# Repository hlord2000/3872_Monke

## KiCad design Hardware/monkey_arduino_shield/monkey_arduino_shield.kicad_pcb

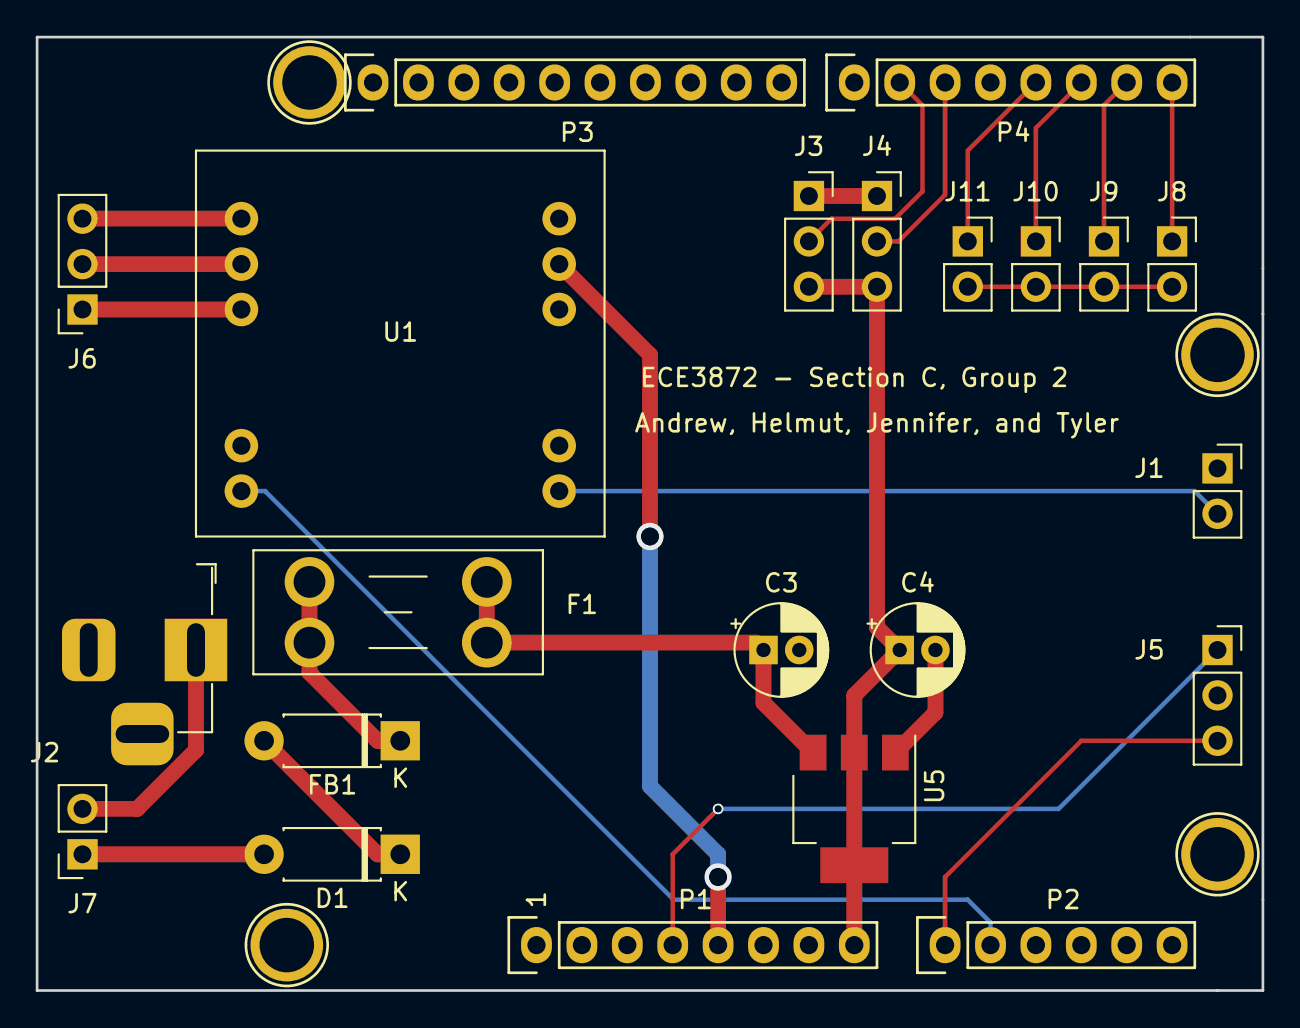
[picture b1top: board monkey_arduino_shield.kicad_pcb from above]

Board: 2 copper layers, 68.6 x 53.3 mm, 26 parts (0 on the bottom side), 21 nets.

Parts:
C3, C4: 10u; CP_Radial_D5.0mm_P2.00mm
D1: B5819W; D_DO-41_SOD81_P7.62mm_Horizontal
F1: 1A; Fuseholder_Blade_Mini_Keystone_3568
FB1: 100 Ohm @ 100 MHz; D_DO-41_SOD81_P7.62mm_Horizontal
J1: Speaker_OUT; PinSocket_1x02_P2.54mm_Vertical
J2: Barrel_Jack; BarrelJack_Horizontal_Helmer_Version
J3: MOTOR_1; PinSocket_1x03_P2.54mm_Vertical
J4: MOTOR_2; PinSocket_1x03_P2.54mm_Vertical
J5: MIC_IN; PinSocket_1x03_P2.54mm_Vertical
J6: POT_IN; PinSocket_1x03_P2.54mm_Vertical
J7: Power_Switch; PinSocket_1x02_P2.54mm_Vertical
J8: IO_Switch_1; PinSocket_1x02_P2.54mm_Vertical
J9: IO_Switch_2; PinSocket_1x02_P2.54mm_Vertical
J10: IO_Switch_3; PinSocket_1x02_P2.54mm_Vertical
J11: IO_Switch_4; PinSocket_1x02_P2.54mm_Vertical
P1: Power; Socket_Strip_Arduino_1x08
P2: Analog; Socket_Strip_Arduino_1x06
P3: Digital; Socket_Strip_Arduino_1x10
P4: Digital; Socket_Strip_Arduino_1x08
P5, P6, P7, P8: CONN_01X01; Arduino_1pin
U1: TPA2005D1-Breakout; TDA_Breakout_Board
U5: AMS1117-5.0; SOT-223-3_TabPin2

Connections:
+3V3: J5.1, P1.4
+5V: P1.5, U1.4
/0(Rx): J8.1, P4.8
/1(Tx): J9.1, P4.7
/2: J10.1, P4.6
/3(**): J11.1, P4.5
/5(**): J4.2, P4.3
/6(**): J3.2, P4.2
/A0: J5.3, P2.1
/A1: P2.2, U1.6
/Vin: C4.1, J3.3, J4.3, P1.8, U5.2
GND: C3.2, C4.2, J1.1, J2.2, J3.1, J4.1, J5.2, J8.2, J9.2, J10.2, J11.2, P1.6, P1.7, P3.4, U1.2, U1.3, U1.7, U5.1
unnamed: C3.1, F1.2, U5.3
unnamed: D1.1, FB1.2
unnamed: D1.2, J7.1
unnamed: F1.1, FB1.1
unnamed: J1.2, U1.1
unnamed: J2.1, J7.2
unnamed: J6.1, U1.8
unnamed: J6.2, U1.9
unnamed: J6.3, U1.10

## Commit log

2021-09-21 dded BOM
2021-09-23 Modified power for motors.
2021-09-23 Hardware Revision in Progress
2021-10-13 Final PCB Revision
2021-10-13 Updated Barrel Jack
